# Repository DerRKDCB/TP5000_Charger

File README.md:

# TP5000_Charger

## TODO

### V1.1

* [x] Test under voltage and short current feature
* [x] rename from LiFePo4 Charger to Lithium Battery Charger
* [x] make select-able between LiFePo4 and LiPo, schematic OK
* [x] fix LEDs to Vin instead of GND, schematic OK
* [x] remove component labels
* [x] tighter layout
* [x] mounting holes in schematic
* [x] smaller solder connections, schematic footprints OK
* [x] USB C side B D+ and D- connections, schematic OK
* [x] change 0805 handsolder to 0805

### V1.2

* [x] missing ground connection C3
* [x] test with lipo
* [x] update silkscreen and schematic version number
* [x] plot gerber

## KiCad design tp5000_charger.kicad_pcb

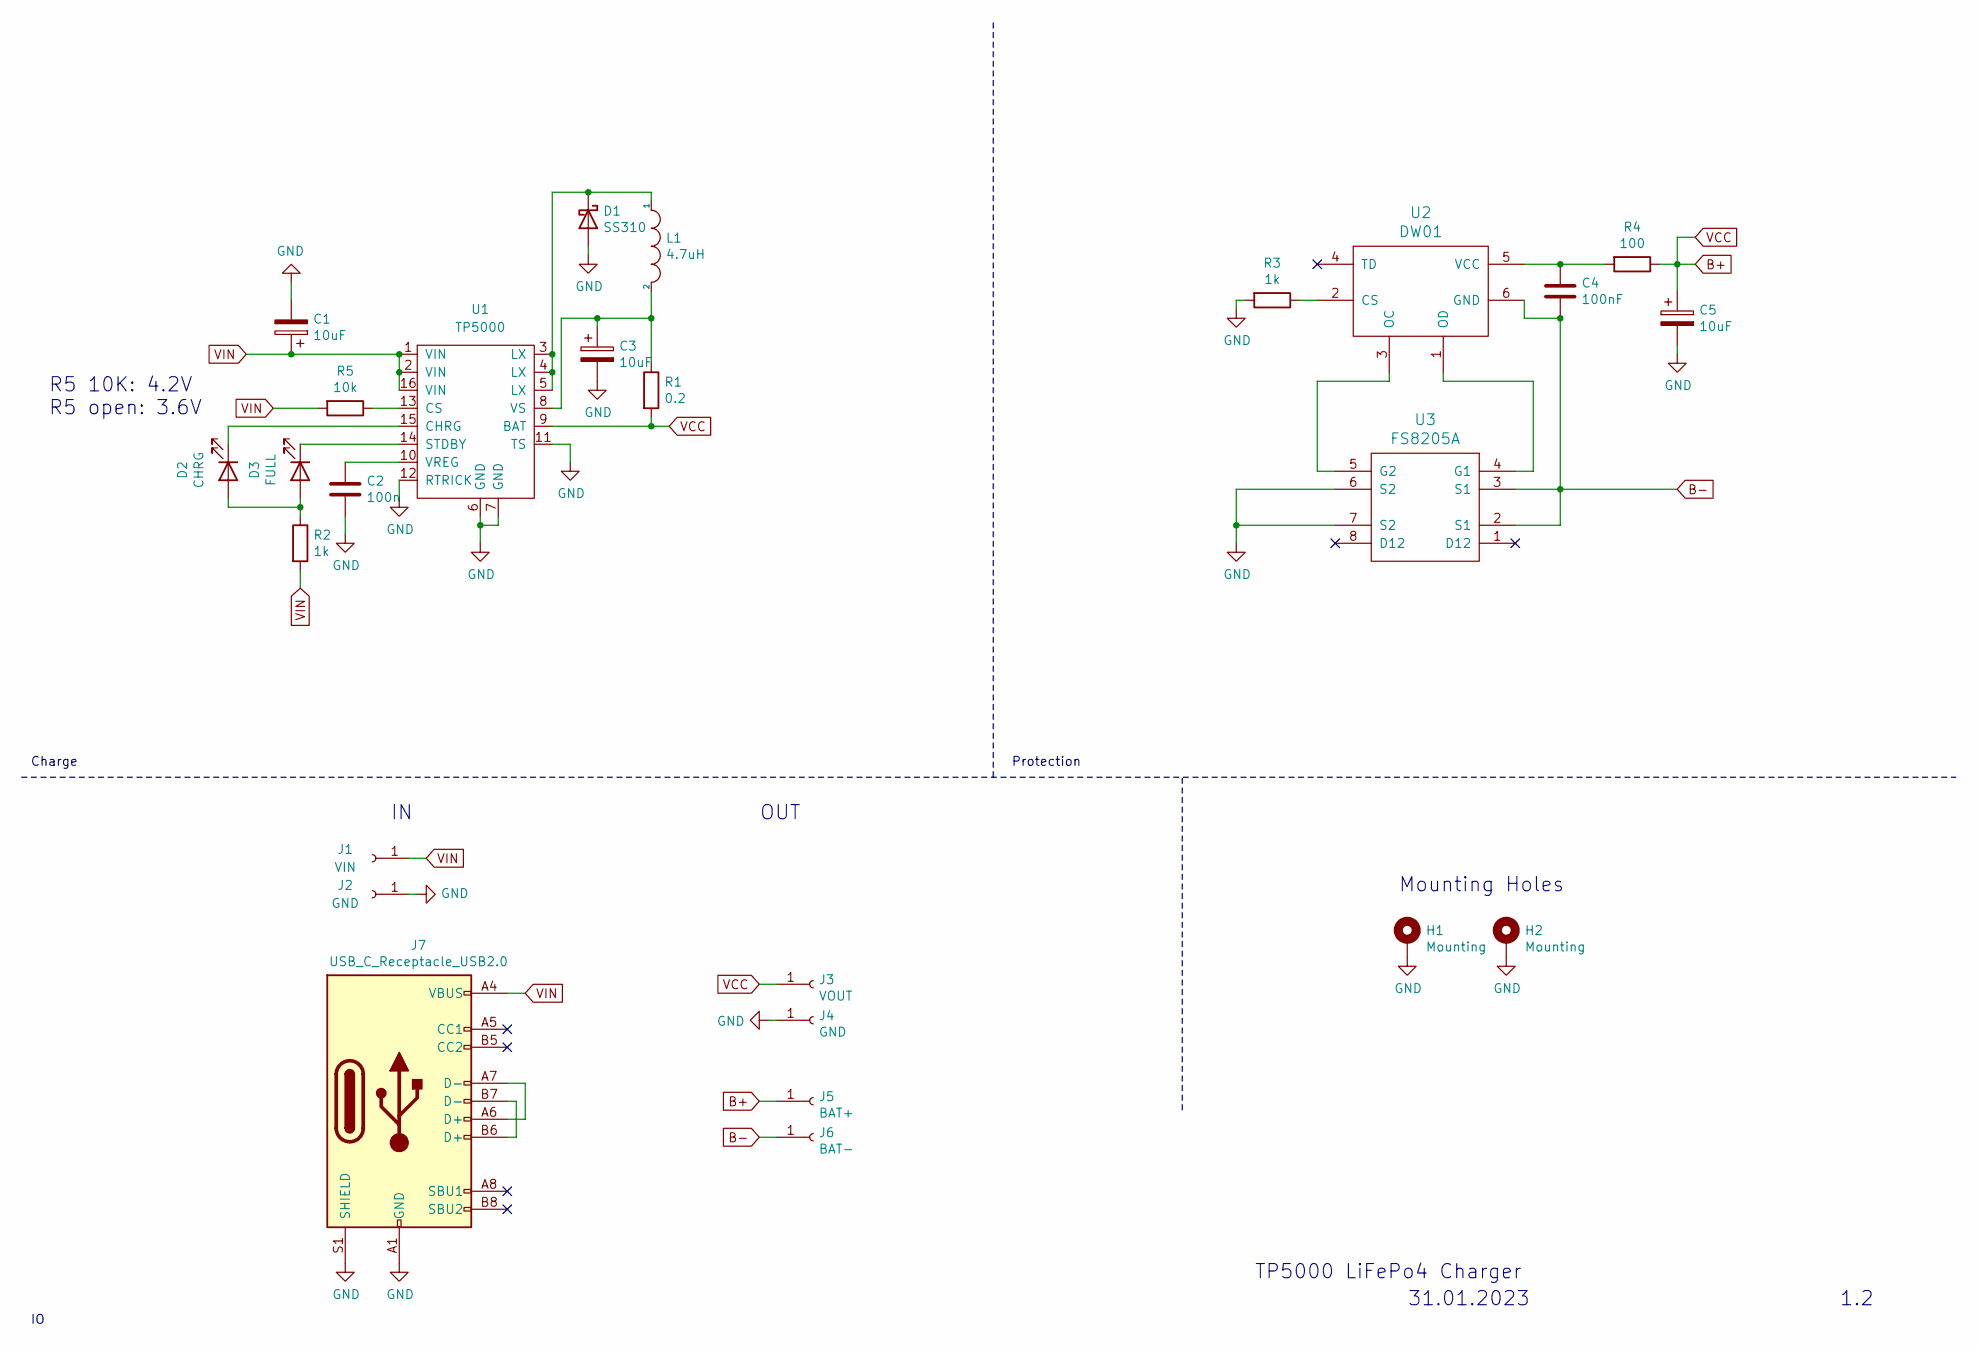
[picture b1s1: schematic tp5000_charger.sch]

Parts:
C1, C3, C5: 10uF; CP_EIA-3216-12_Kemet-S
C2: 100n; C_0805_2012Metric
C4: 100nF; C_0805_2012Metric
D1: SS310; D_SMA
D2: CHRG; LED_0805_2012Metric
D3: FULL; LED_0805_2012Metric
H1, H2: Mounting; MountingHole_2.7mm_M2.5_DIN965_Pad
J1: VIN; TestPoint_THTPad_2.5x2.5mm_Drill1.2mm
J2, J4: GND; TestPoint_THTPad_2.5x2.5mm_Drill1.2mm
J3: VOUT; TestPoint_THTPad_2.5x2.5mm_Drill1.2mm
J5: BAT+; TestPoint_THTPad_2.5x2.5mm_Drill1.2mm
J6: BAT-; TestPoint_THTPad_2.5x2.5mm_Drill1.2mm
J7: USB_C_Receptacle_USB2.0; USB_C_Receptacle_Palconn_UTC16-G
L1: 4.7uH; L_Taiyo-Yuden_NR-50xx
R1: 0.2; R_1206_3216Metric_Pad1.30x1.75mm_HandSolder
R2, R3: 1k; R_0805_2012Metric
R4: 100; R_0805_2012Metric
R5: 10k; R_0805_2012Metric
U1: TP5000; QFN-16-1EP_4x4mm_P0.65mm_EP2.1x2.1mm
U2: DW01; SOT-23-6
U3: FS8205A; TSSOP-8_4.4x3mm_P0.65mm

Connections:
B+: C5.1, J3.1, J5.1, R1.2, R4.1, U1.9 (BAT)
B-: C4.2, J6.1, U2.6 (GND), U3.2 (S1), U3.3 (S1)
GND: C1.2, C2.2, C3.2, C5.2, D1.2 (A), H1.1, H2.1, J2.1, J4.1, J7.A1 (GND), J7.A12 (GND), J7.B1 (GND), J7.B12 (GND), J7.S1 (SHIELD), R3.2, U1.6 (GND), U1.7 (GND), U1.11 (TS), U1.12 (RTRICK), U3.6 (S2), U3.7 (S2)
unnamed: C2.1, U1.10 (VREG)
unnamed: C3.1, L1.2, R1.1, U1.8 (VS)
unnamed: C4.1, R4.2, U2.5 (VCC)
unnamed: D1.1 (K), L1.1, U1.3 (LX), U1.4 (LX), U1.5 (LX)
unnamed: D2.1 (K), U1.15 (CHRG)
unnamed: D2.2 (A), D3.2 (A), R2.1
unnamed: D3.1 (K), U1.14 (STDBY)
unnamed: J7.A6 (D+), J7.A7 (D-)
unnamed: J7.B6 (D+), J7.B7 (D-)
unnamed: R3.1, U2.2 (CS)
unnamed: R5.1, U1.13 (CS)
unnamed: U2.1 (OD), U3.4 (G1)
unnamed: U2.3 (OC), U3.5 (G2)
VIN: C1.1, J1.1, J7.A4 (VBUS), J7.A9 (VBUS), J7.B4 (VBUS), J7.B9 (VBUS), R2.2, R5.2, U1.1 (VIN), U1.2 (VIN), U1.16 (VIN)

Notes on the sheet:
Charge
Protection
1.2
31.01.2023
TP5000 LiFePo4 Charger
R5 10K: 4.2V R5 open: 3.6V
Mounting Holes
OUT

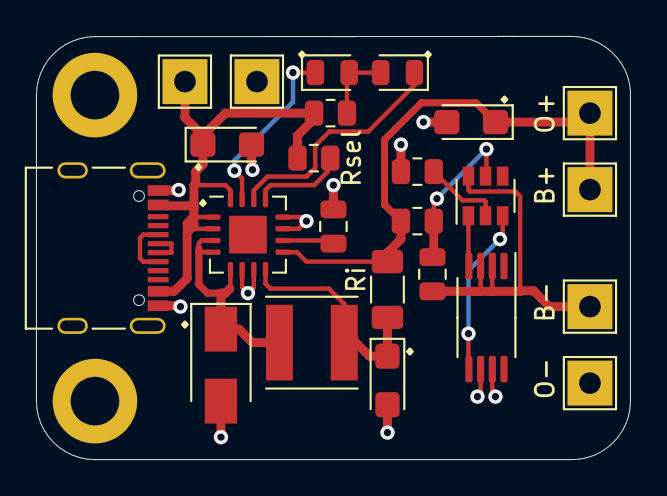
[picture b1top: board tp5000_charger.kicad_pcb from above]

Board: 2 copper layers, 33.0 x 23.5 mm, 26 parts (0 on the bottom side), 17 nets.

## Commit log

2023-03-08 formating
2023-03-08 checkboxes
2023-03-08 changed footprint solder connection in schematic
2023-03-08 add gitignore
2023-03-08 remove .gitignore files
2023-03-08 remove unneccecary files
2023-03-14 change file name to tp500_charger
2023-03-14 select 3.6 vs 4.2V
2023-03-14 mounting holes
2023-03-14 pcb design V1.1
2023-03-19 layout smaller
2023-03-19 create gerber files
2023-04-29 todo v1.2
2023-04-29 gnd connection c3
2023-04-29 version number 1.2
2023-07-09 library update
2023-07-09 generate gerber files
2023-07-09 polarity indicator d1
